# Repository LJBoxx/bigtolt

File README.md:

# BigTOLT - Big(kinda) esc with TOLT mosfets

18 mosfet TOLT package esc design based off vesc6 schematic and compatible with [VESC](https://github.com/vedderb/bldc) firmware.

There is also a small high voltage converter used for higher voltage operation, aim was to have a quite big voltage operation range. But if you will test it with high voltage, please do mind that the voltage sensing is **un-isolated**

# Untested !!
This board is not tested but the pcb is ready for prototype. BOM and gerber are in [here](/tolt)

## Board preview

## Liability
This project sources are provided **as is** therfore I, and the co controbutors to this repository shall not be held responsible for any damage occured, including but not limited to hardware damages or other physical injury caused by the outcomes of this source. **You are responsible for your actions. If used wrong, it will go wrong!**

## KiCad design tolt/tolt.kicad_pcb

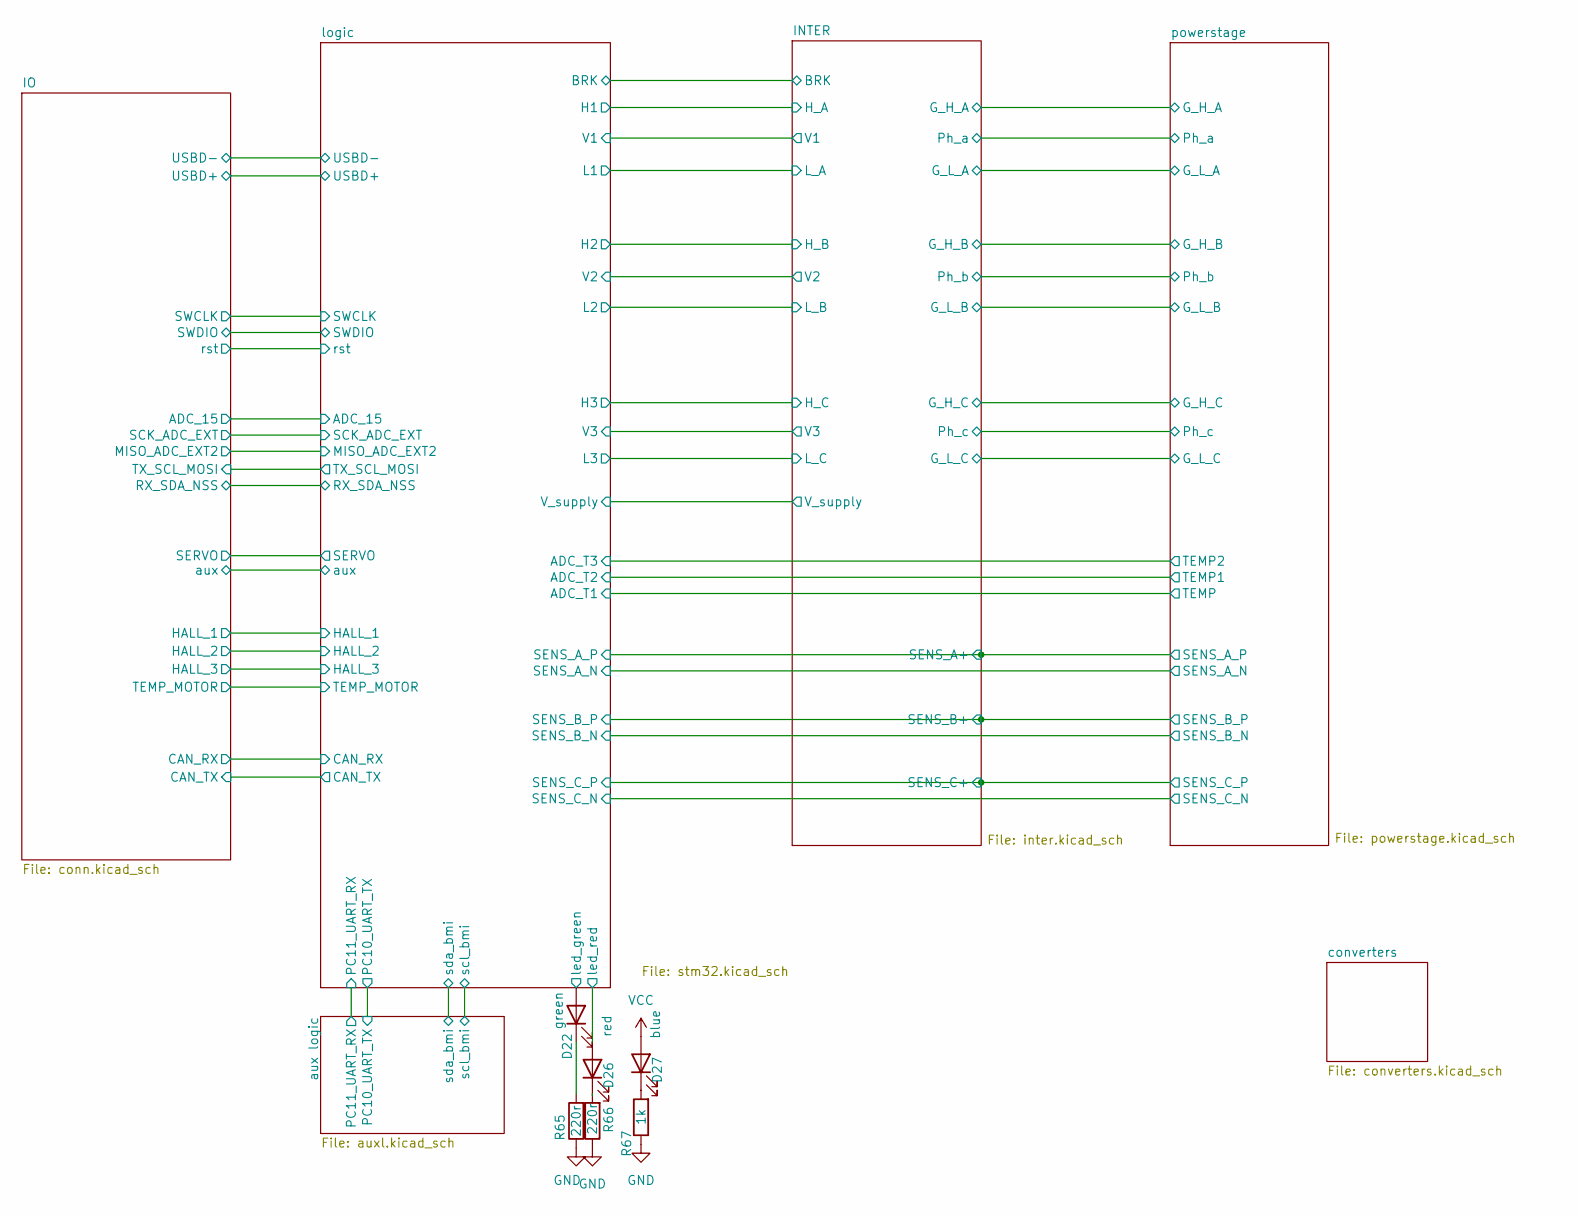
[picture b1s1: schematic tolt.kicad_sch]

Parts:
D22: green; D_0603_1608Metric_Pad1.05x0.95mm_HandSolder
D26: red; D_0603_1608Metric_Pad1.05x0.95mm_HandSolder
D27: blue; D_0603_1608Metric_Pad1.05x0.95mm_HandSolder
R65, R66: 220r; R_0603_1608Metric
R67: 1k; R_0603_1608Metric

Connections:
/logic/led_green: D22.2 (A); also elsewhere on the board
/logic/led_red: D26.2 (A); also elsewhere on the board
GND: R65.1, R66.1, R67.1; also elsewhere on the board
unnamed: D22.1 (K), R65.2
unnamed: D26.1 (K), R66.2
unnamed: D27.1 (K), R67.2
VCC: D27.2 (A); also elsewhere on the board

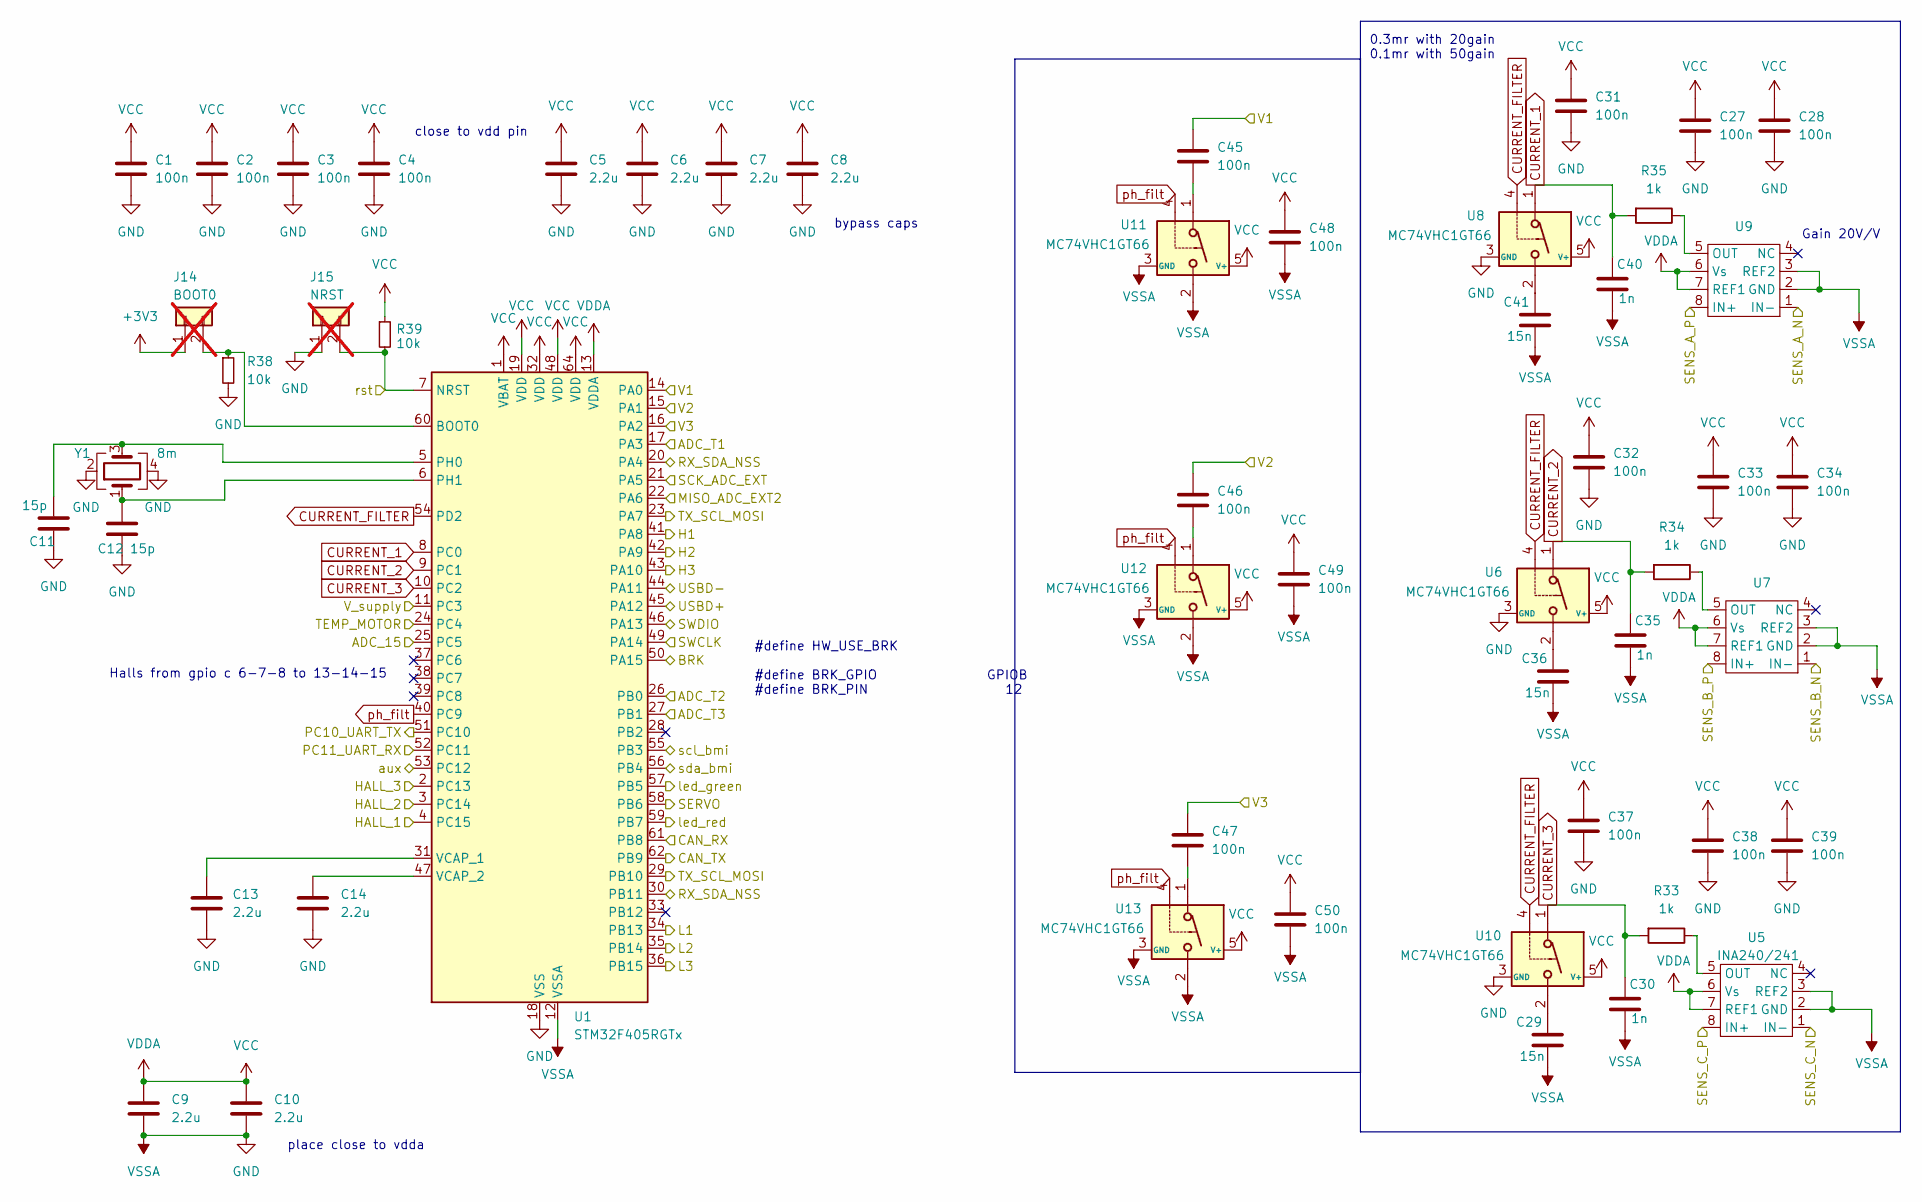
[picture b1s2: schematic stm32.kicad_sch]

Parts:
C1, C2, C3, C4, C27, C28, C31, C32, C33, C34, C37, C38, C39, C45, C46, C47, C48, C49, C50: 100n; C_0402_1005Metric
C5, C6, C7, C8, C9, C10, C13, C14: 2.2u; C_0603_1608Metric
C11, C12: 15p; C_0402_1005Metric
C29, C36, C41: 15n; C_0603_1608Metric
C30, C35, C40: 1n; C_0603_1608Metric
J14: BOOT0; SolderJumper-2_P1.3mm_Open_RoundedPad1.0x1.5mm; not fitted
J15: NRST; SolderJumper-2_P1.3mm_Open_RoundedPad1.0x1.5mm; not fitted
R33, R34, R35: 1k; R_0603_1608Metric
R38, R39: 10k; R_0603_1608Metric; LCSC C25804
U1: STM32F405RGTx; LQFP-64_10x10mm_P0.5mm
U5: INA240/241; SOT-23-8
U6, U8, U10, U11, U12, U13: MC74VHC1GT66; SOT-353_SC-70-5
U7, U9: SOT-23-8
Y1: 8m; Crystal_SMD_3225-4Pin_3.2x2.5mm

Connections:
+3V3: J14.1
/INTER/BRK: U1.50 (PA15); also elsewhere on the board
/INTER/H_A: U1.41 (PA8); also elsewhere on the board
/INTER/H_B: U1.42 (PA9); also elsewhere on the board
/INTER/H_C: U1.43 (PA10); also elsewhere on the board
/INTER/L_A: U1.34 (PB13); also elsewhere on the board
/INTER/L_B: U1.35 (PB14); also elsewhere on the board
/INTER/L_C: U1.36 (PB15); also elsewhere on the board
/INTER/V1: C45.2, U1.14 (PA0); also elsewhere on the board
/INTER/V2: C46.2, U1.15 (PA1); also elsewhere on the board
/INTER/V3: C47.2, U1.16 (PA2); also elsewhere on the board
/INTER/V_supply: U1.11 (PC3); also elsewhere on the board
/IO/ADC_15: U1.25 (PC5); also elsewhere on the board
/IO/CAN_RX: U1.61 (PB8); also elsewhere on the board
/IO/CAN_TX: U1.62 (PB9); also elsewhere on the board
/IO/HALL_1: U1.4 (PC15); also elsewhere on the board
/IO/HALL_2: U1.3 (PC14); also elsewhere on the board
/IO/HALL_3: U1.2 (PC13); also elsewhere on the board
/IO/MISO_ADC_EXT2: U1.22 (PA6); also elsewhere on the board
/IO/RX_SDA_NSS: U1.20 (PA4), U1.30 (PB11); also elsewhere on the board
/IO/SCK_ADC_EXT: U1.21 (PA5); also elsewhere on the board
/IO/SERVO: U1.58 (PB6); also elsewhere on the board
/IO/SWCLK: U1.49 (PA14); also elsewhere on the board
/IO/SWDIO: U1.46 (PA13); also elsewhere on the board
/IO/TEMP_MOTOR: U1.24 (PC4); also elsewhere on the board
/IO/TX_SCL_MOSI: U1.23 (PA7), U1.29 (PB10); also elsewhere on the board
/IO/USBD+: U1.45 (PA12); also elsewhere on the board
/IO/USBD-: U1.44 (PA11); also elsewhere on the board
/IO/aux: U1.53 (PC12); also elsewhere on the board
/IO/rst: J15.2, R39.2, U1.7 (NRST); also elsewhere on the board
/aux logic/scl_bmi: U1.55 (PB3); also elsewhere on the board
/aux logic/sda_bmi: U1.56 (PB4); also elsewhere on the board
/logic/ADC_T1: U1.17 (PA3); also elsewhere on the board
/logic/ADC_T2: U1.26 (PB0); also elsewhere on the board
/logic/ADC_T3: U1.27 (PB1); also elsewhere on the board
/logic/PC10_UART_TX: U1.51 (PC10)
/logic/PC11_UART_RX: U1.52 (PC11)
/logic/led_green: U1.57 (PB5); also elsewhere on the board
/logic/led_red: U1.59 (PB7); also elsewhere on the board
CURRENT_1: C40.1, R35.2, U1.8 (PC0), U8.1
CURRENT_2: C35.1, R34.2, U1.9 (PC1), U6.1
CURRENT_3: C30.1, R33.2, U1.10 (PC2), U10.1
CURRENT_FILTER: U1.54 (PD2), U6.4, U8.4, U10.4
GND: C1.1, C2.1, C3.1, C4.1, C5.1, C6.1, C7.1, C8.1, C9.1, C10.1, C11.2, C12.2, C13.1, C14.1, C27.1, C28.1, C29.2, C30.2, C31.1, C32.1, C33.1, C34.1, C35.2, C36.2, C37.1, C38.1, C39.1, C40.2, C41.2, C48.1, C49.1, C50.1, J15.1, R38.2, U1.12 (VSSA), U1.18 (VSS), U1.63 (VSS), U5.2 (GND), U5.3 (REF2), U6.3 (GND), U7.2 (GND), U7.3 (REF2), U8.3 (GND), U9.2 (GND), U9.3 (REF2), U10.3 (GND), U11.2, U11.3 (GND), U12.2, U12.3 (GND), U13.2, U13.3 (GND), Y1.2, Y1.4; also elsewhere on the board
unnamed: C29.1, U10.2
unnamed: C36.1, U6.2
unnamed: C41.1, U8.2
unnamed: C45.1, U11.1
unnamed: C46.1, U12.1
unnamed: C47.1, U13.1
unnamed: J14.2, R38.1, U1.60 (BOOT0)
unnamed: C11.1, U1.5 (PH0), Y1.3
unnamed: C12.1, U1.6 (PH1), Y1.1
unnamed: C13.2, U1.31 (VCAP_1)
unnamed: C14.2, U1.47 (VCAP_2)
unnamed: R33.1, U5.5 (OUT)
unnamed: R34.1, U7.5 (OUT)
unnamed: R35.1, U9.5 (OUT)
SENS_A_N: U9.1 (IN-); also elsewhere on the board
SENS_A_P: U9.8 (IN+); also elsewhere on the board
SENS_B_N: U7.1 (IN-); also elsewhere on the board
SENS_B_P: U7.8 (IN+); also elsewhere on the board
SENS_C_N: U5.1 (IN-); also elsewhere on the board
SENS_C_P: U5.8 (IN+); also elsewhere on the board
VCC: C1.2, C2.2, C3.2, C4.2, C5.2, C6.2, C7.2, C8.2, C9.2, C10.2, C27.2, C28.2, C31.2, C32.2, C33.2, C34.2, C37.2, C38.2, C39.2, C48.2, C49.2, C50.2, R39.1, U1.1 (VBAT), U1.13 (VDDA), U1.19 (VDD), U1.32 (VDD), U1.48 (VDD), U1.64 (VDD), U5.6 (Vs), U5.7 (REF1), U6.5 (V+), U7.6 (Vs), U7.7 (REF1), U8.5 (V+), U9.6 (Vs), U9.7 (REF1), U10.5 (V+), U11.5 (V+), U12.5 (V+), U13.5 (V+); also elsewhere on the board
ph_filt: U1.40 (PC9), U11.4, U12.4, U13.4

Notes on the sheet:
close to vdd pin
0.3mr with 20gain 0.1mr with 50gain
place close to vdda
#define HW_USE_BRK #define BRK_GPIO GPIOB #define BRK_PIN 12
Gain 20V/V
Halls from gpio c 6-7-8 to 13-14-15
bypass caps

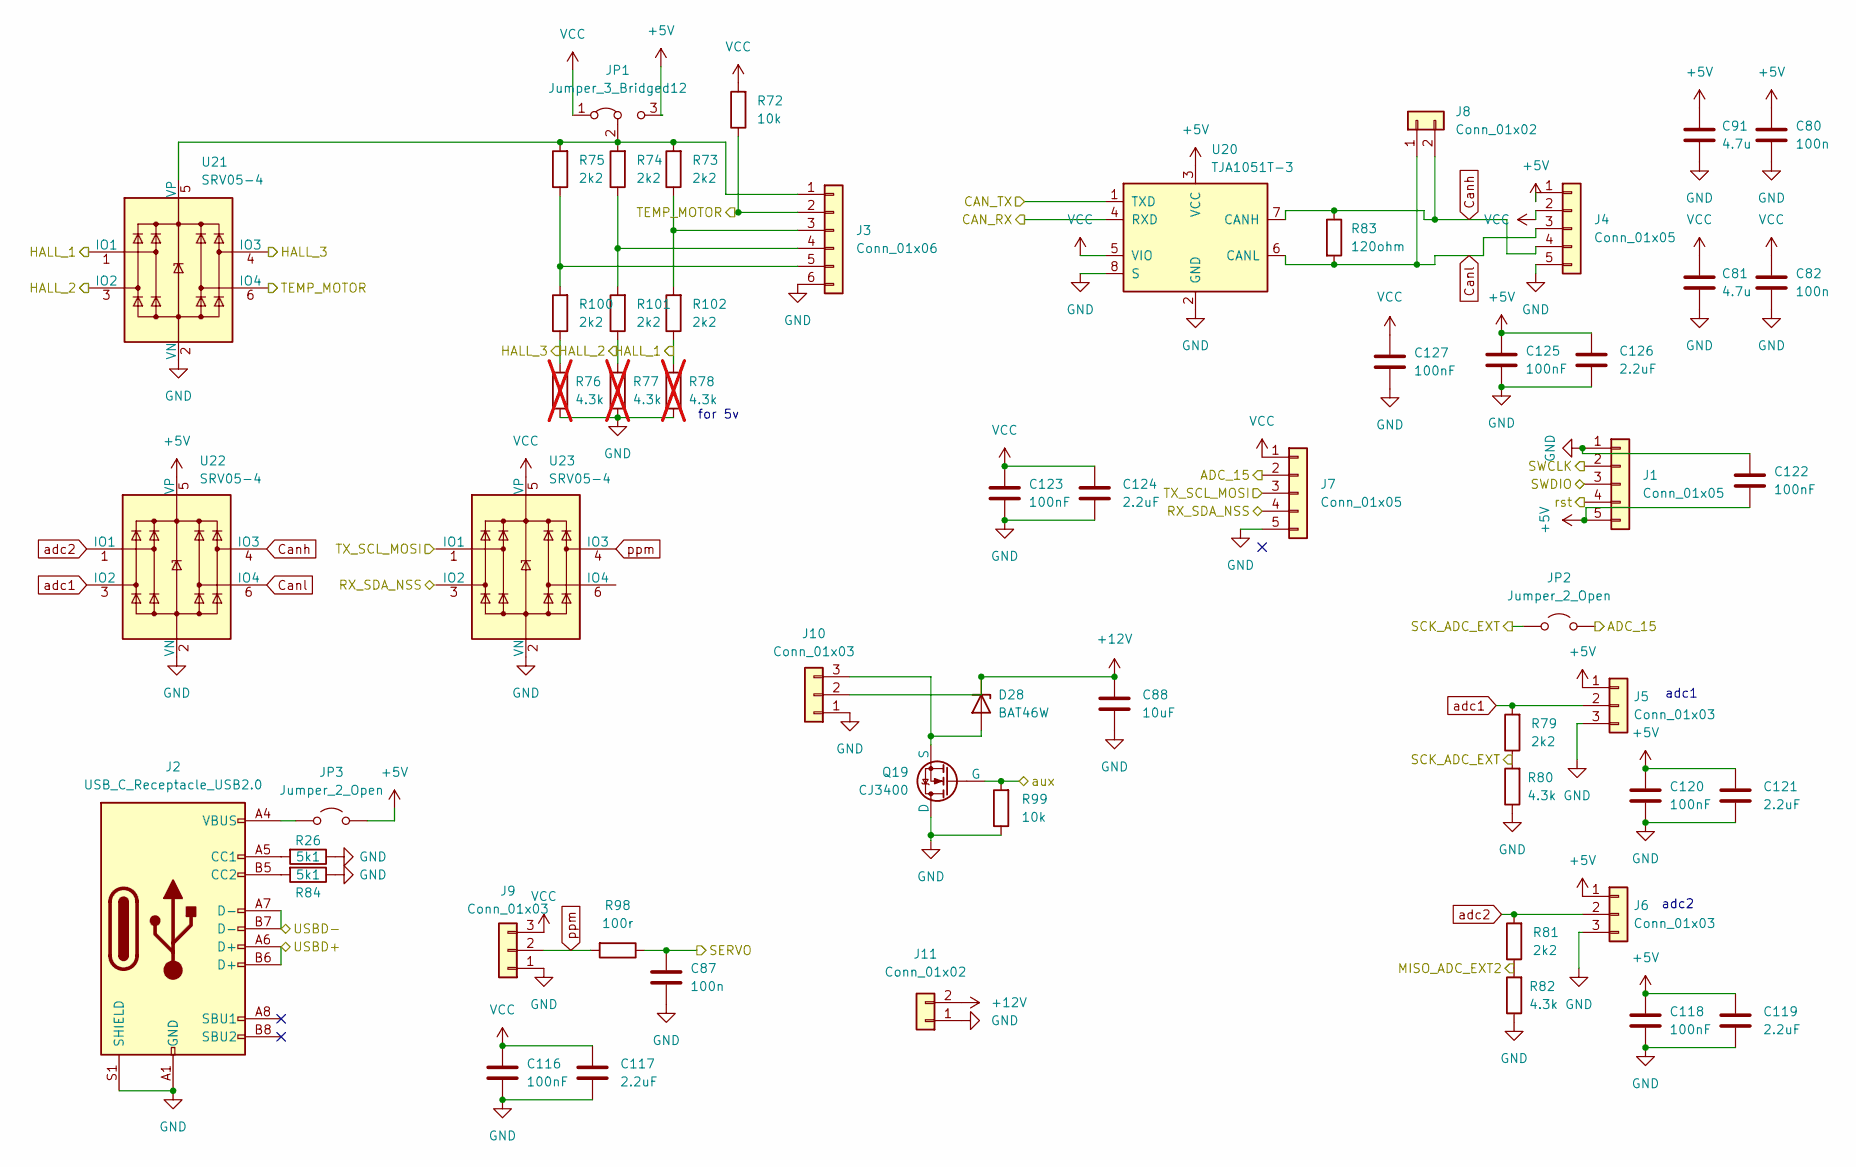
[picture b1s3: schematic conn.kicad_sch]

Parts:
C80, C82, C87: 100n; C_0402_1005Metric
C81, C91: 4.7u; C_0805_2012Metric
C88: 10uF; C_1210_3225Metric
C116, C118, C120, C122, C123, C125, C127: 100nF; C_0402_1005Metric
C117, C119, C121, C124, C126: 2.2uF; C_1210_3225Metric
D28: BAT46W; D_SOD-323F
J1: Conn_01x05; PinSocket_1x05_P2.00mm_Vertical
J2: USB_C_Receptacle_USB2.0; USB_C_Receptacle_G-Switch_GT-USB-7051x
J3: Conn_01x06; JST_PH_B6B-PH-K_1x06_P2.00mm_Vertical
J4, J7: Conn_01x05; JST_PH_B5B-PH-K_1x05_P2.00mm_Vertical
J5, J6, J9, J10: Conn_01x03; JST_PH_B3B-PH-K_1x03_P2.00mm_Vertical
J8: Conn_01x02; JST_PH_B2B-PH-K_1x02_P2.00mm_Vertical
J11: Conn_01x02; JST_XH_B2B-XH-A_1x02_P2.50mm_Vertical
JP1: Jumper_3_Bridged12; SolderJumper-3_P1.3mm_Bridged2Bar12_RoundedPad1.0x1.5mm
JP2, JP3: Jumper_2_Open; SolderJumper-2_P1.3mm_Open_RoundedPad1.0x1.5mm
Q19: CJ3400; SOT-23
R26, R84: 5k1; R_0603_1608Metric
R72, R99: 10k; R_0603_1608Metric
R73, R74, R75, R79, R81, R100, R101, R102: 2k2; R_0603_1608Metric
R76, R77, R78: 4.3k; R_0603_1608Metric; not fitted
R80, R82: 4.3k; R_0603_1608Metric
R83: 120ohm; R_0603_1608Metric
R98: 100r; R_0603_1608Metric
U20: TJA1051T-3; SOIC-8_3.9x4.9mm_P1.27mm
U21, U22, U23: SRV05-4; SOT-23-6

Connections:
+5V: C80.2, C91.2, C118.1, C119.1, C120.1, C121.1, C122.2, C125.1, C126.1, J1.5, J4.1, J5.1, J6.1, JP1.3 (B), JP3.2 (B), U20.3 (VCC), U22.5 (VP); also elsewhere on the board
+12V: C88.2, D28.1 (K), J10.2, J11.2; also elsewhere on the board
/IO/ADC_15: J7.2, JP2.2 (B); also elsewhere on the board
/IO/CAN_RX: U20.4 (RXD); also elsewhere on the board
/IO/CAN_TX: U20.1 (TXD); also elsewhere on the board
/IO/HALL_1: R78.2, R102.1, U21.1 (IO1); also elsewhere on the board
/IO/HALL_2: R77.2, R101.1, U21.3 (IO2); also elsewhere on the board
/IO/HALL_3: R76.2, R100.1, U21.4 (IO3); also elsewhere on the board
/IO/MISO_ADC_EXT2: R81.1, R82.2; also elsewhere on the board
/IO/RX_SDA_NSS: J7.4; also elsewhere on the board
/IO/SCK_ADC_EXT: JP2.1 (A), R79.1, R80.2; also elsewhere on the board
/IO/SERVO: C87.2, R98.1; also elsewhere on the board
/IO/SWCLK: J1.2; also elsewhere on the board
/IO/SWDIO: J1.3; also elsewhere on the board
/IO/TEMP_MOTOR: J3.2, R72.1, U21.6 (IO4); also elsewhere on the board
/IO/TX_SCL_MOSI: J7.3; also elsewhere on the board
/IO/USBD+: J2.A6 (D+), J2.B6 (D+); also elsewhere on the board
/IO/USBD-: J2.A7 (D-), J2.B7 (D-); also elsewhere on the board
/IO/aux: Q19.2 (G), R99.2; also elsewhere on the board
/IO/rst: J1.4; also elsewhere on the board
Canh: J4.4, J8.2, R83.1, U20.7 (CANH), U22.4 (IO3)
Canl: J4.3, J8.1, R83.2, U20.6 (CANL), U22.6 (IO4)
GND: C80.1, C81.1, C82.1, C87.1, C88.1, C91.1, C116.2, C117.2, C118.2, C119.2, C120.2, C121.2, C122.1, C123.2, C124.2, C125.2, C126.2, C127.2, J1.1, J2.A1 (GND), J2.A12 (GND), J2.B1 (GND), J2.B12 (GND), J2.S1 (SHIELD), J3.6, J4.5, J5.3, J6.3, J7.5, J9.1, J10.1, J11.1, Q19.1 (D), R26.1, R76.1, R77.1, R78.1, R80.1, R82.1, R84.1, R99.1, U20.2 (GND), U20.8 (S), U21.2 (VN), U22.2 (VN), U23.2 (VN); also elsewhere on the board
unnamed: D28.2 (A), J10.3, Q19.3 (S)
unnamed: J2.A5 (CC1), R26.2
unnamed: J2.B5 (CC2), R84.2
unnamed: J3.1, JP1.2 (C), R73.2, R74.2, R75.2, U21.5 (VP)
unnamed: J3.3, R73.1, R102.2
unnamed: J3.4, R74.1, R101.2
unnamed: J3.5, R75.1, R100.2
unnamed: J2.A4 (VBUS), J2.A9 (VBUS), J2.B4 (VBUS), J2.B9 (VBUS), JP3.1 (A)
VCC: C81.2, C82.2, C116.1, C117.1, C123.1, C124.1, C127.1, J4.2, J7.1, J9.3, JP1.1 (A), R72.2, U20.5 (VIO), U23.5 (VP); also elsewhere on the board
adc1: J5.2, R79.2, U22.3 (IO2)
adc2: J6.2, R81.2, U22.1 (IO1)
ppm: J9.2, R98.2, U23.4 (IO3)

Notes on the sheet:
adc2
adc1
for 5v

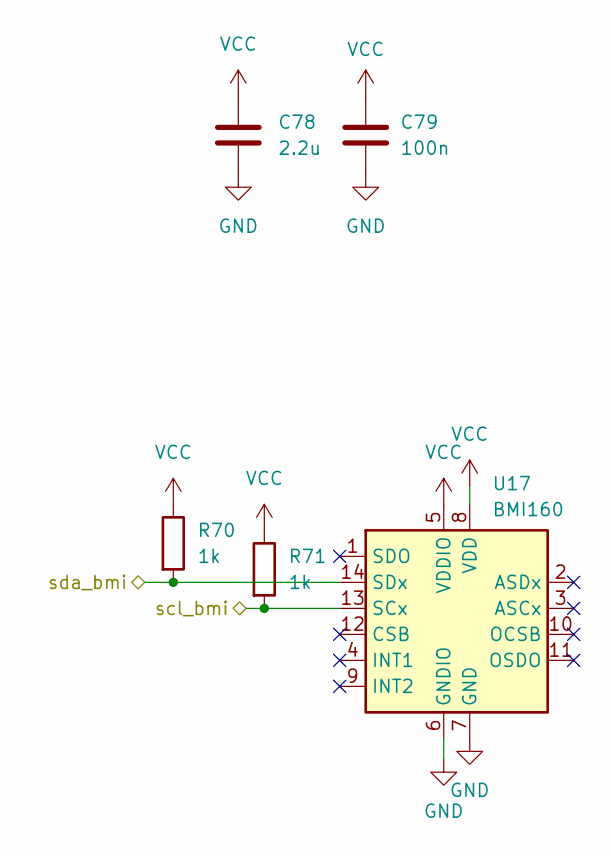
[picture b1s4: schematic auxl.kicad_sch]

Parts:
C78: 2.2u; C_0603_1608Metric
C79: 100n; C_0402_1005Metric
R70, R71: 1k; R_0603_1608Metric
U17: BMI160; Bosch_LGA-14_3x2.5mm_P0.5mm

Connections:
/aux logic/scl_bmi: R71.2, U17.13 (SCx); also elsewhere on the board
/aux logic/sda_bmi: R70.2, U17.14 (SDx); also elsewhere on the board
GND: C78.1, C79.1, U17.6 (GNDIO), U17.7 (GND); also elsewhere on the board
VCC: C78.2, C79.2, R70.1, R71.1, U17.5 (VDDIO), U17.8 (VDD); also elsewhere on the board

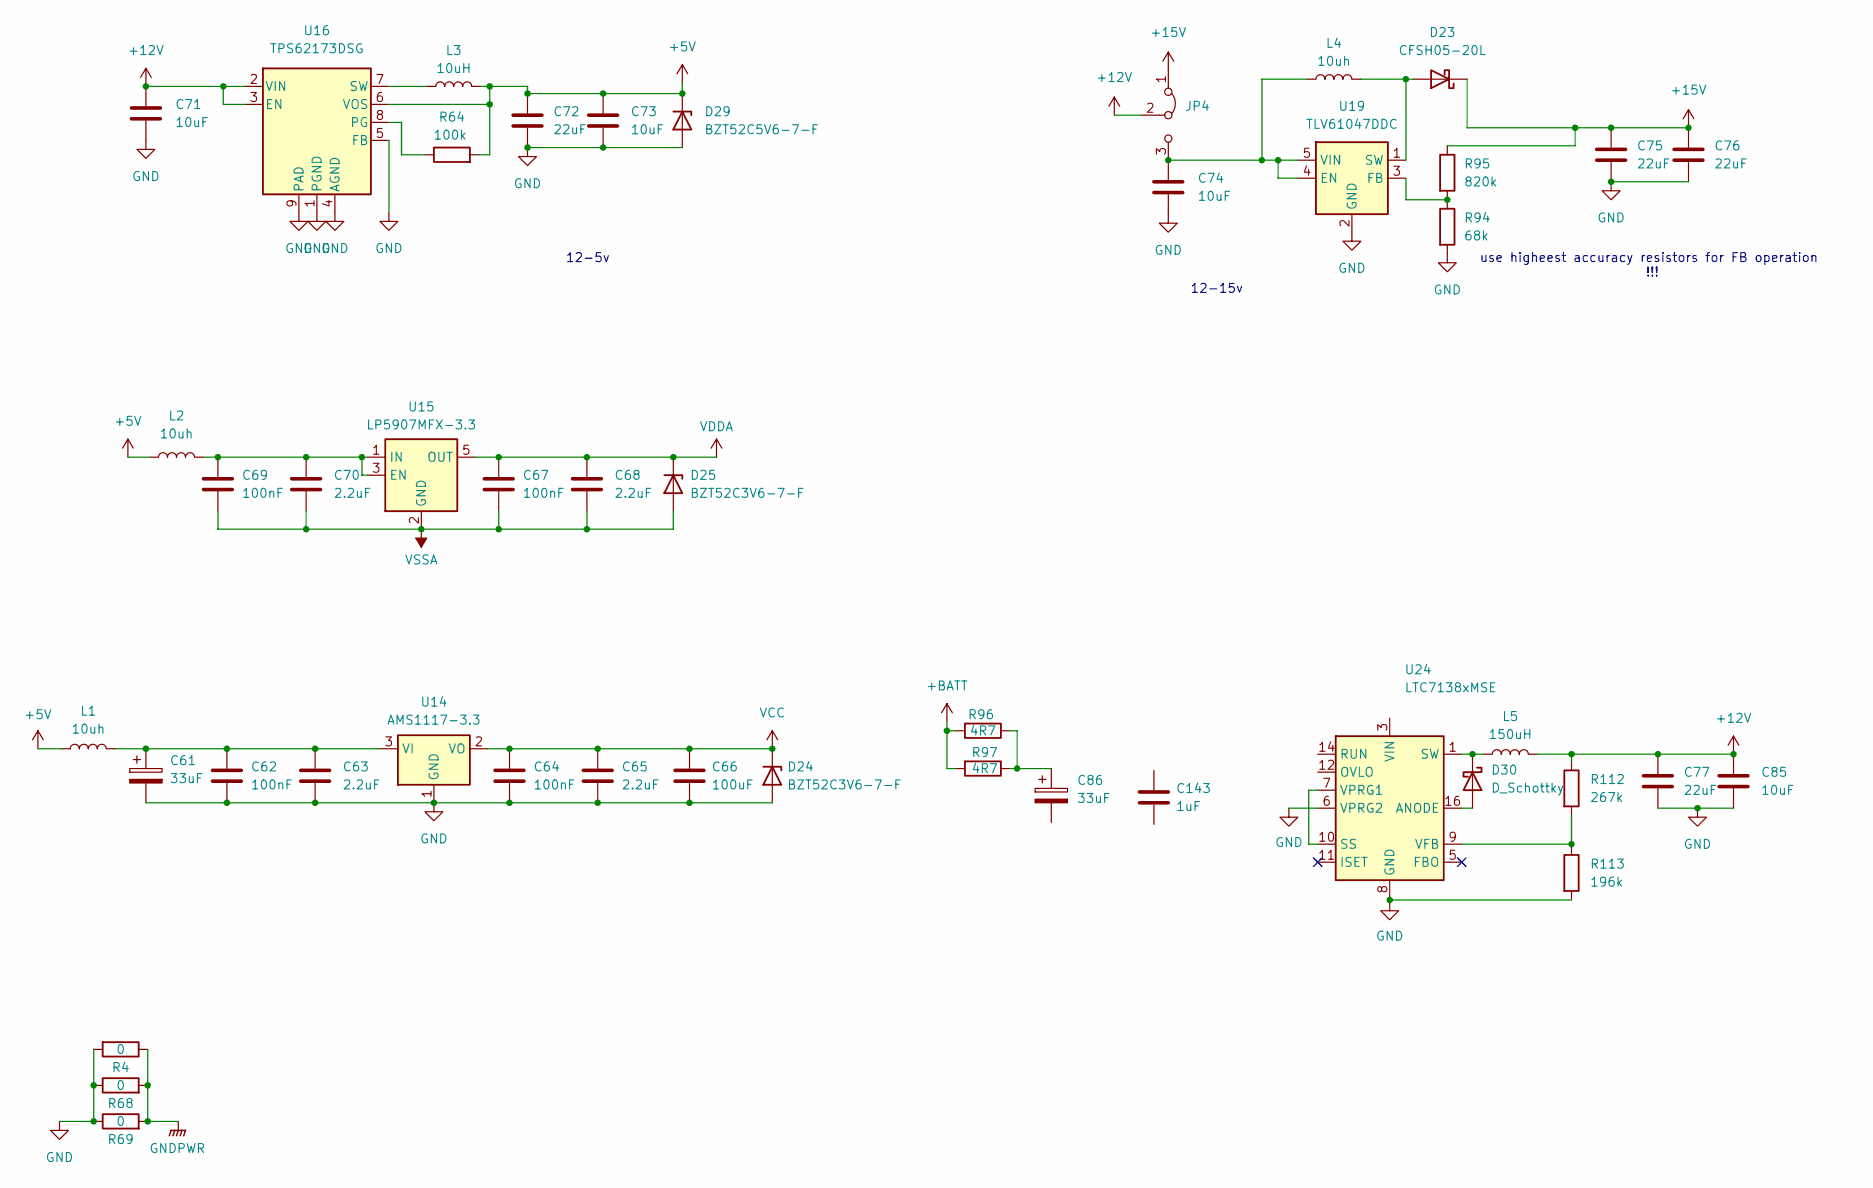
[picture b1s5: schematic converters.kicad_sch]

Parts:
C61: 33uF; CP_Elec_4x5.4
C62, C64, C67, C69: 100nF; C_0402_1005Metric
C63, C65, C68, C70: 2.2uF; C_1210_3225Metric
C66: 100uF; C_0402_1005Metric
C71, C73, C74, C85: 10uF; C_1210_3225Metric
C72, C75, C76, C77: 22uF; C_1210_3225Metric; part TAJB226K016RNJ
C86: 33uF
C143: 1uF
D23: CFSH05-20L; D_SOD-882
D24, D25: BZT52C3V6-7-F; D_SOD-123
D29: BZT52C5V6-7-F; D_SOD-123
D30: D_Schottky
JP4: Jumper_3_Bridged12; SolderJumper-3_P1.3mm_Bridged2Bar12_RoundedPad1.0x1.5mm
L1, L2: 10uh; IND-SMD_L3.9-W3.9-1
L3: 10uH; IND-SMD_L5.0-W5.0
L4: 10uh; L_Abracon_ASPI-4030S
L5: 150uH
R4, R68, R69: 0; R_0815_2038Metric
R64: 100k; R_0603_1608Metric
R94: 68k; R_0603_1608Metric
R95: 820k; R_0603_1608Metric
R96, R97: 4R7; R_0805_2012Metric; LCSC C17675
R112: 267k
R113: 196k
U14: AMS1117-3.3; SOT-223-3_TabPin2
U15: LP5907MFX-3.3; SOT-23-5
U16: TPS62173DSG; WSON-8-1EP_2x2mm_P0.5mm_EP0.9x1.6mm
U19: TLV61047DDC; SOT-23-5
U24: LTC7138xMSE; Analog_MSOP-12-16-1EP_3x4.039mm_P0.5mm_EP1.651x2.845mm

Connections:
+5V: C72.2, C73.2, D29.1 (K), L1.1, L2.1, L3.2, R64.2, U16.6 (VOS); also elsewhere on the board
+12V: C71.2, C77.2, C85.2, JP4.2 (C), L5.2, R112.1, U16.2 (VIN), U16.3 (EN); also elsewhere on the board
+15V: C75.2, C76.2, D23.1 (K), JP4.1 (A), R95.1; also elsewhere on the board
GND: C61.2, C62.2, C63.2, C64.2, C65.2, C66.2, C67.2, C68.2, C69.2, C70.2, C71.1, C72.1, C73.1, C74.1, C75.1, C76.1, C77.1, C85.1, D24.2 (A), D25.2 (A), D29.2 (A), R4.2, R68.1, R69.1, R94.2, R113.2, U14.1 (GND), U15.2 (GND), U16.1 (PGND), U16.4 (AGND), U16.5 (FB), U16.9 (PAD), U19.2 (GND), U24.6 (VPRG2), U24.8 (GND), U24.17 (GND); also elsewhere on the board
GNDPWR: R4.1, R68.2, R69.2; also elsewhere on the board
unnamed: C86.1, R96.1, R97.1
unnamed: D23.2 (A), L4.2, U19.1 (SW)
unnamed: D30.1 (K), L5.1, U24.1 (SW)
unnamed: D30.2 (A), U24.16 (ANODE)
unnamed: C74.2, JP4.3 (B), L4.1, U19.4 (EN), U19.5 (VIN)
unnamed: R96.2, R97.2
unnamed: R112.2, R113.1, U24.9 (VFB)
unnamed: C61.1, C62.1, C63.1, L1.2, U14.3 (VI)
unnamed: C69.1, C70.1, L2.2, U15.1 (IN), U15.3 (EN)
unnamed: R64.1, U16.8 (PG)
unnamed: L3.1, U16.7 (SW)
unnamed: R94.1, R95.2, U19.3 (FB)
unnamed: U24.7 (VPRG1), U24.10 (SS)
VCC: C64.1, C65.1, C66.1, C67.1, C68.1, D24.1 (K), D25.1 (K), U14.2 (VO), U15.5 (OUT); also elsewhere on the board

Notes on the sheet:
12-15v
12-5v
use higheest accuracy resistors for FB operation !!!

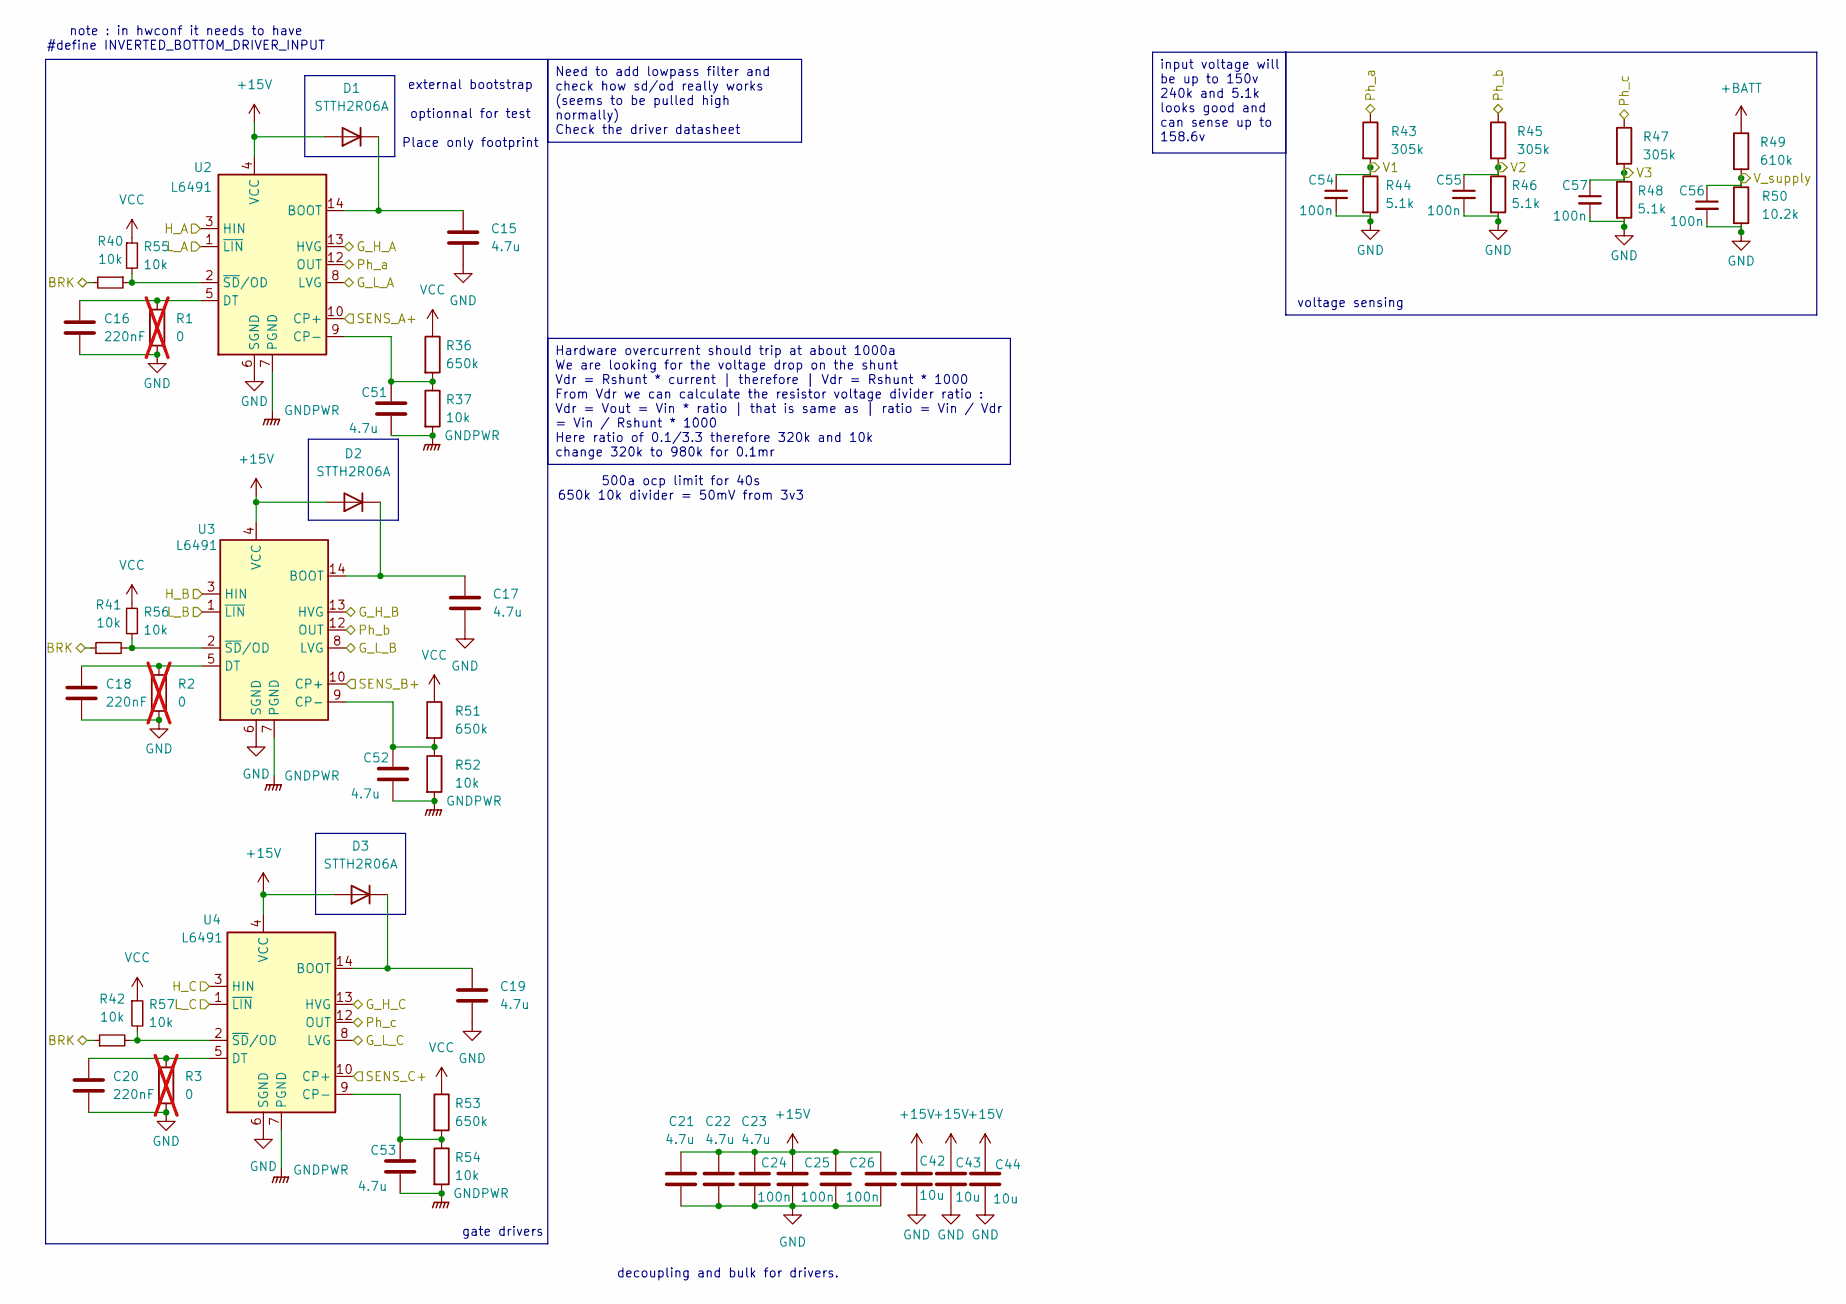
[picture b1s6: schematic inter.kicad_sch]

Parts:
C15, C17, C19, C21, C22, C23: 4.7u; C_0805_2012Metric
C16, C18, C20: 220nF; C_0402_1005Metric
C24, C25, C26: 100n; C_0402_1005Metric
C42, C43, C44: 10u; C_1210_3225Metric_Pad1.33x2.70mm_HandSolder
C51, C52, C53: 4.7u; C_0603_1608Metric
C54, C55, C56, C57: 100n; C_0603_1608Metric
D1, D2, D3: STTH2R06A; D_SMA
R1, R2, R3: 0; R_0603_1608Metric; not fitted
R36, R51, R53: 650k; R_0603_1608Metric
R37, R52, R54: 10k; R_0603_1608Metric
R40, R41, R42, R55, R56, R57: 10k; R_0603_1608Metric; LCSC C25804
R43, R45, R47: 305k; R_1206_3216Metric
R44, R46, R48: 5.1k; R_0603_1608Metric
R49: 610k; R_1206_3216Metric
R50: 10.2k; R_0603_1608Metric
U2, U3, U4: L6491; SO-14_3.9x8.65mm_P1.27mm

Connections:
+15V: C21.2, C22.2, C23.2, C24.2, C25.2, C26.2, C42.1, C43.1, C44.1, D1.2 (A), D2.2 (A), D3.2 (A), U2.4 (VCC), U3.4 (VCC), U4.4 (VCC); also elsewhere on the board
+BATT: R49.1; also elsewhere on the board
/INTER/BRK: R40.2, R41.1, R42.1; also elsewhere on the board
/INTER/G_H_A: U2.13 (HVG); also elsewhere on the board
/INTER/G_H_B: U3.13 (HVG); also elsewhere on the board
/INTER/G_H_C: U4.13 (HVG); also elsewhere on the board
/INTER/G_L_A: U2.8 (LVG); also elsewhere on the board
/INTER/G_L_B: U3.8 (LVG); also elsewhere on the board
/INTER/G_L_C: U4.8 (LVG); also elsewhere on the board
/INTER/H_A: U2.3 (HIN); also elsewhere on the board
/INTER/H_B: U3.3 (HIN); also elsewhere on the board
/INTER/H_C: U4.3 (HIN); also elsewhere on the board
/INTER/L_A: U2.1 (~LIN); also elsewhere on the board
/INTER/L_B: U3.1 (~LIN); also elsewhere on the board
/INTER/L_C: U4.1 (~LIN); also elsewhere on the board
/INTER/Ph_a: R43.1, U2.12 (OUT); also elsewhere on the board
/INTER/Ph_b: R45.1, U3.12 (OUT); also elsewhere on the board
/INTER/Ph_c: R47.1, U4.12 (OUT); also elsewhere on the board
/INTER/V1: C54.1, R43.2, R44.1; also elsewhere on the board
/INTER/V2: C55.1, R45.2, R46.1; also elsewhere on the board
/INTER/V3: C57.1, R47.2, R48.1; also elsewhere on the board
/INTER/V_supply: C56.1, R49.2, R50.1; also elsewhere on the board
GND: C15.2, C16.1, C17.2, C18.1, C19.2, C20.1, C21.1, C22.1, C23.1, C24.1, C25.1, C26.1, C42.2, C43.2, C44.2, C54.2, C55.2, C56.2, C57.2, R1.2, R2.2, R3.2, R44.2, R46.2, R48.2, R50.2, U2.6 (SGND), U3.6 (SGND), U4.6 (SGND); also elsewhere on the board
GNDPWR: C51.2, C52.2, C53.2, R37.2, R52.2, R54.2, U2.7 (PGND), U3.7 (PGND), U4.7 (PGND); also elsewhere on the board
unnamed: C15.1, D1.1 (K), U2.14 (BOOT)
unnamed: C17.1, D2.1 (K), U3.14 (BOOT)
unnamed: C19.1, D3.1 (K), U4.14 (BOOT)
unnamed: C51.1, R36.2, R37.1, U2.9 (CP-)
unnamed: C16.2, R1.1, U2.5 (DT)
unnamed: R40.1, R55.2, U2.2 (~SD/OD)
unnamed: C52.1, R51.2, R52.1, U3.9 (CP-)
unnamed: C18.2, R2.1, U3.5 (DT)
unnamed: R41.2, R56.2, U3.2 (~SD/OD)
unnamed: C53.1, R53.2, R54.1, U4.9 (CP-)
unnamed: C20.2, R3.1, U4.5 (DT)
unnamed: R42.2, R57.2, U4.2 (~SD/OD)
SENS_A_P: U2.10 (CP+); also elsewhere on the board
SENS_B_P: U3.10 (CP+); also elsewhere on the board
SENS_C_P: U4.10 (CP+); also elsewhere on the board
VCC: R36.1, R51.1, R53.1, R55.1, R56.1, R57.1; also elsewhere on the board

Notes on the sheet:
voltage sensing
gate drivers
note : in hwconf it needs to have #define INVERTED_BOTTOM_DRIVER_INPUT
external bootstrap optionnal for test Place only footprint
decoupling and bulk for drivers.
500a ocp limit for 40s 650k 10k divider = 50mV from 3v3
Need to add lowpass filter and check how sd/od really works (seems to be pulled high normally) Check the driver datasheet
input voltage will be up to 150v 240k and 5.1k looks good and can sense up to 158.6v
Hardware overcurrent should trip at about 1000a We are looking for the voltage drop on the shunt Vdr = Rshunt * current | therefore | Vdr = Rshunt * 1000 From Vdr we can calculate the resistor voltage divider ratio : Vdr = Vout = Vin * ratio | that is same as | ratio = Vin / Vdr = Vin / Rshunt * 10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
